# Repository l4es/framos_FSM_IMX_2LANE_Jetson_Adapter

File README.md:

# framos_FSM_IMX_2LANE_Jetson_Adapter

Adapter for Framos FSM (Sony IMX based) camera modules to Raspberry Pi 15-pin camera interface, available in official Nvidia Jetson Developer Kits

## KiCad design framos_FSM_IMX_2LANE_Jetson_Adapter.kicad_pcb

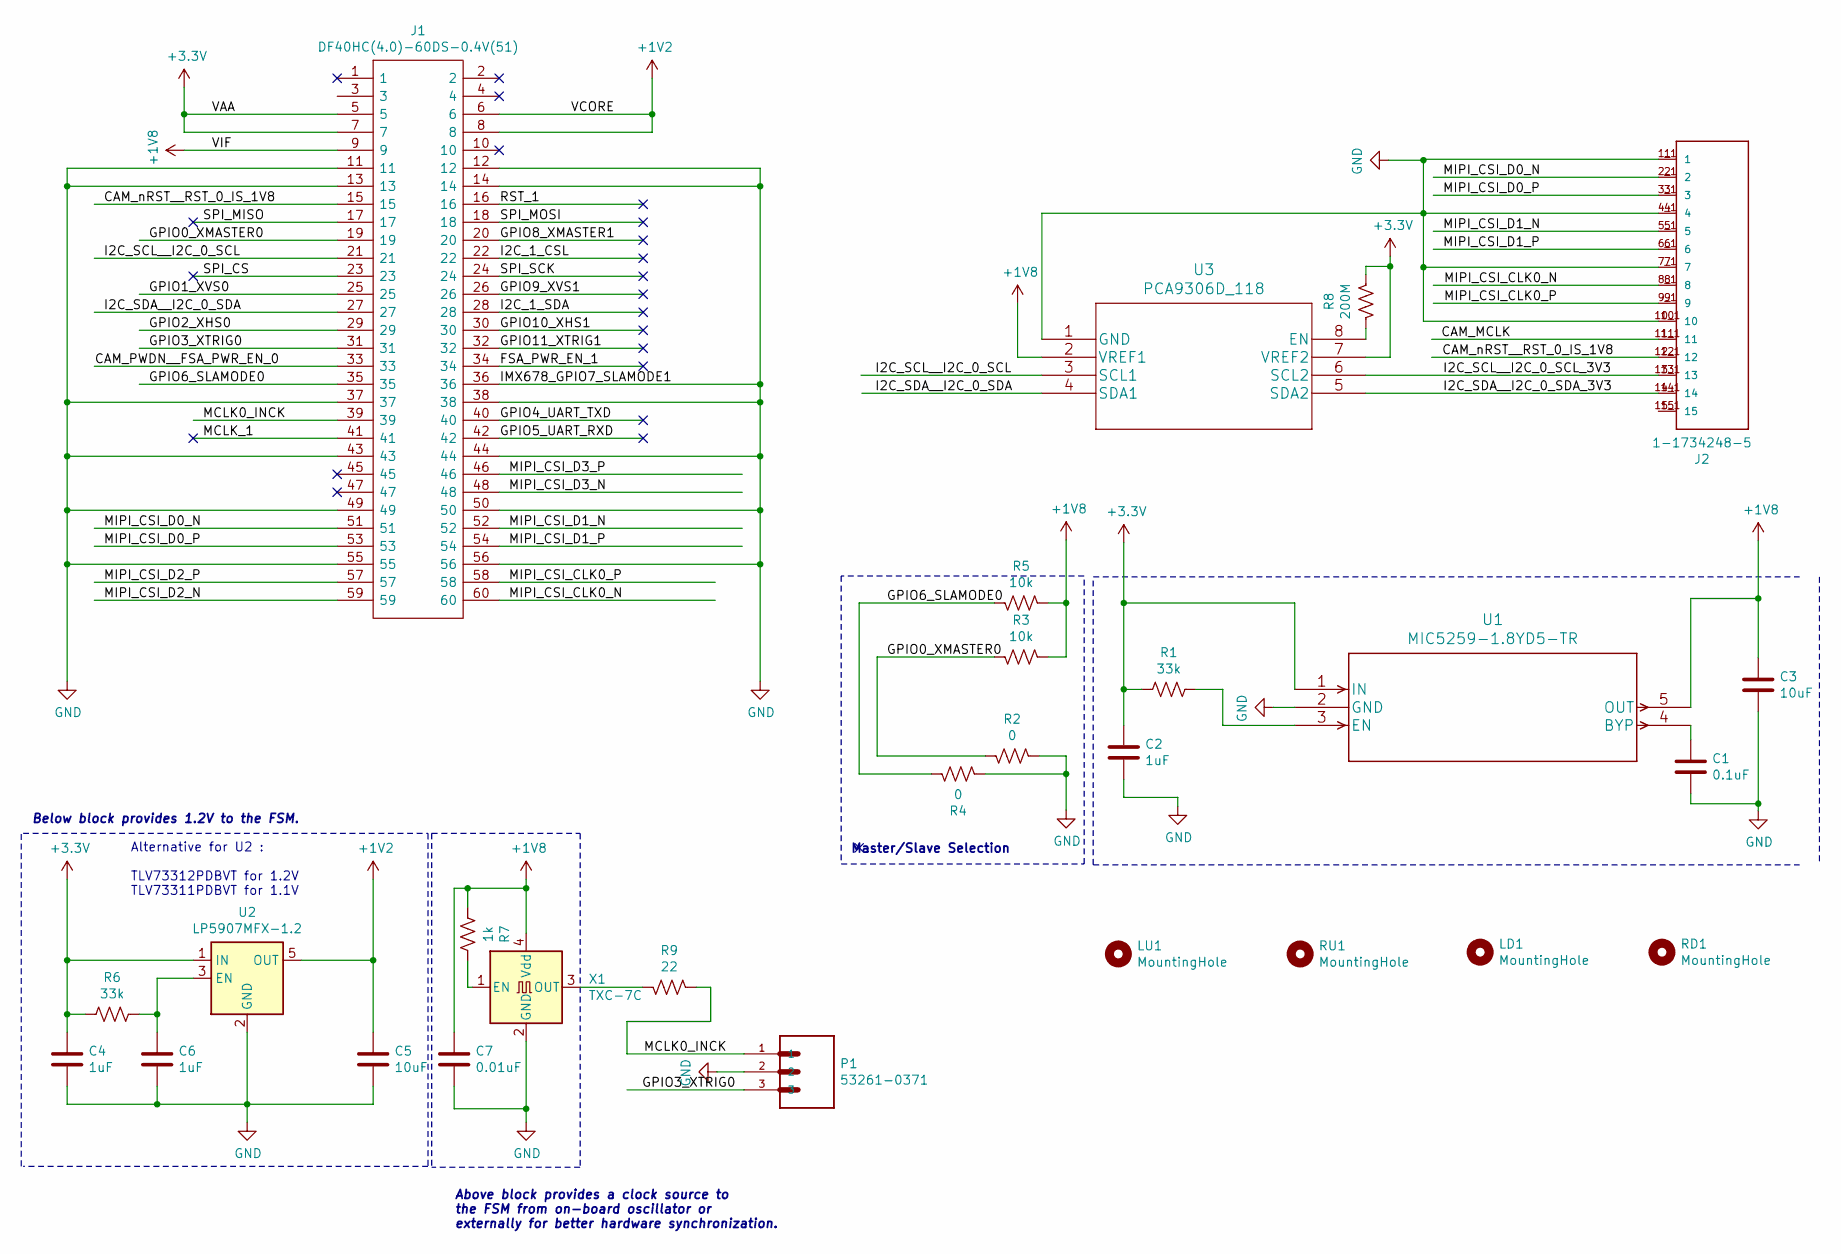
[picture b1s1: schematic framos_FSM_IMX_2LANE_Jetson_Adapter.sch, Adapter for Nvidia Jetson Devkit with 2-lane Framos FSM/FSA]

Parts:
C1: 0.1uF; C_0603_1608Metric
C2, C4, C6: 1uF; C_0603_1608Metric
C3, C5: 10uF; C_0603_1608Metric
C7: 0.01uF; C_0603_1608Metric
J1: DF40HC(4.0)-60DS-0.4V(51); DF40HC4060DS04V51; Manufacturer_Part_Number DF40HC(4.0)-60DS-0.4V(51); Mouser Part Number 798-DF4HC4060DS04V51
J2: 1-1734248-5; TE_1-1734248-5
LD1: MountingHole; MountingHole_2.2mm_M2_ISO14580_Pad
LU1: MountingHole; MountingHole_2.2mm_M2_ISO14580_Pad
P1: 53261-0371; MOLEX_53261-0371
R1, R6: 33k; R_0603_1608Metric
R2, R4: 0; R_0603_1608Metric
R3, R5: 10k; R_0603_1608Metric
R7: 1k; R_0603_1608Metric
R8: 200M; R_0603_1608Metric
R9: 22; R_0603_1608Metric
RD1: MountingHole; MountingHole_2.2mm_M2_ISO14580_Pad
RU1: MountingHole; MountingHole_2.2mm_M2_ISO14580_Pad
U1: MIC5259-1.8YD5-TR; MIC5259-2.8YD5-TR
U2: LP5907MFX-1.2; SOT-23-5
U3: PCA9306D_118; PCA9306D
X1: TXC-7C; Oscillator_SMD_TXC_7C-4Pin_5.0x3.2mm

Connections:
+1V2: C5.1, J1.6, J1.8, U2.5 (OUT)
+1V8: C3.1, C7.1, J1.9, R3.2, R5.2, R7.2, U1.5 (OUT), U3.2 (VREF1), X1.4 (Vdd)
/CAM_MCLK: J2.11, J2.11_1 (11)
/CAM_PWDN__FSA_PWR_EN_0: J1.33
/CAM_nRST__RST_0_IS_1V8: J1.15, J2.12, J2.12_1 (12)
/FSA_PWR_EN_1: J1.34
/GPIO0_XMASTER0: J1.19, R2.1, R3.1
/GPIO1_XVS0: J1.25
/GPIO2_XHS0: J1.29
/GPIO3_XTRIG0: J1.31, P1.3
/GPIO4_UART_TXD: J1.40
/GPIO5_UART_RXD: J1.42
/GPIO6_SLAMODE0: J1.35, R4.2, R5.1
/GPIO8_XMASTER1: J1.20
/GPIO9_XVS1: J1.26
/GPIO10_XHS1: J1.30
/GPIO11_XTRIG1: J1.32
/I2C_1_CSL: J1.22
/I2C_1_SDA: J1.28
/I2C_SCL__I2C_0_SCL: J1.21, U3.3 (SCL1)
/I2C_SCL__I2C_0_SCL_3V3: J2.13, J2.13_1 (13), U3.6 (SCL2)
/I2C_SDA__I2C_0_SDA: J1.27, U3.4 (SDA1)
/I2C_SDA__I2C_0_SDA_3V3: J2.14, J2.14_1 (14), U3.5 (SDA2)
/MCLK0_INCK: J1.39, P1.1, R9.2
/MCLK_1: J1.41
/MIPI_CSI_CLK0_N: J1.60, J2.8, J2.8_1 (8)
/MIPI_CSI_CLK0_P: J1.58, J2.9, J2.9_1 (9)
/MIPI_CSI_D0_N: J1.51, J2.2, J2.2_1 (2)
/MIPI_CSI_D0_P: J1.53, J2.3, J2.3_1 (3)
/MIPI_CSI_D1_N: J1.52, J2.5, J2.5_1 (5)
/MIPI_CSI_D1_P: J1.54, J2.6, J2.6_1 (6)
/MIPI_CSI_D2_N: J1.59
/MIPI_CSI_D2_P: J1.57
/MIPI_CSI_D3_N: J1.48
/MIPI_CSI_D3_P: J1.46
/RST_1: J1.16
/SPI_CS: J1.23
/SPI_MISO: J1.17
/SPI_MOSI: J1.18
/SPI_SCK: J1.24
GND: C1.2, C2.2, C3.2, C4.2, C5.2, C6.2, C7.2, J1.11, J1.12, J1.13, J1.14, J1.36, J1.37, J1.38, J1.43, J1.44, J1.49, J1.50, J1.55, J1.56, J2.1, J2.1_1 (1), J2.4, J2.4_1 (4), J2.7, J2.7_1 (7), J2.10, J2.10_1 (10), P1.2, R2.2, R4.1, U1.2 (GND), U2.2 (GND), U3.1 (GND), X1.2 (GND)
unnamed: C1.1, U1.4 (BYP)
unnamed: C6.1, R6.1, U2.3 (EN)
unnamed: R1.1, U1.3 (EN)
unnamed: R7.1, X1.1 (EN)
unnamed: R8.1, U3.8 (EN)
unnamed: R9.1, X1.3 (OUT)

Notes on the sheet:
Alternative for U2 : TLV73312PDBVT for 1.2V TLV73311PDBVT for 1.1V
Below block provides 1.2V to the FSM.
Above block provides a clock source to the FSM from on-board oscillator or externally for better hardware synchronization.
Master/Slave Selection

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
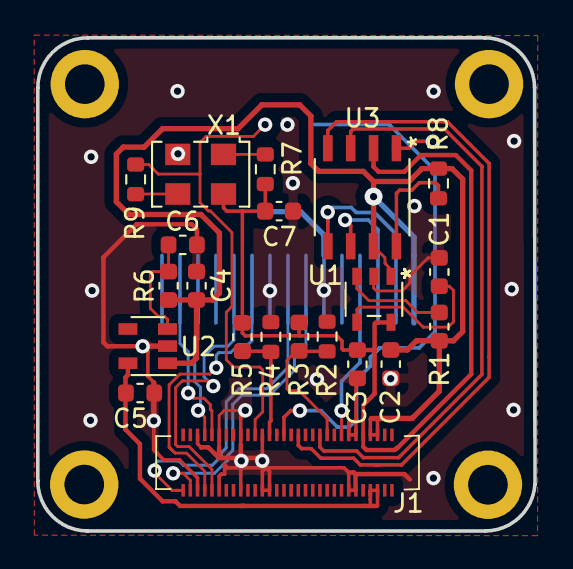
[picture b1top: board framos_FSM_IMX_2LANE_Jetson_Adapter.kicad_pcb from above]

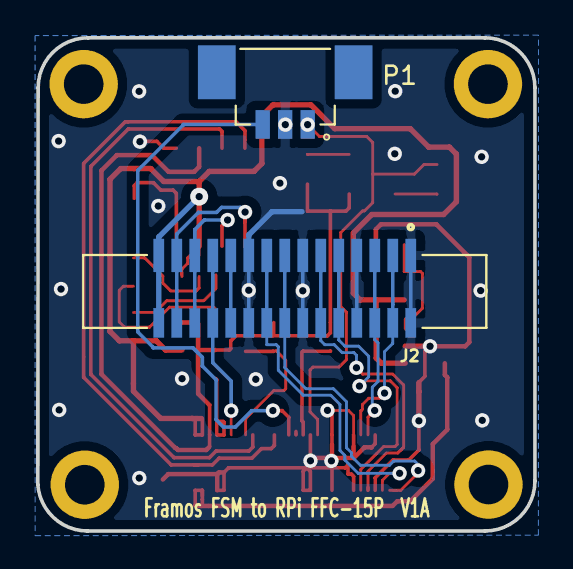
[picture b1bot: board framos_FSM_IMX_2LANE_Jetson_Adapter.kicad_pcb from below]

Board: 2 copper layers, 27.6 x 27.4 mm, 27 parts (2 on the bottom side), 26 nets.

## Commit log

2024-08-09 Add V1A version
2024-08-09 Add 3V3 power supply from J2
2024-08-09 Add documentation
2024-08-09 Update documentation to show board's images

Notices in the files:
parts and their libraries:
Copyright 2021 Accelerated Designs. All rights reserved.
